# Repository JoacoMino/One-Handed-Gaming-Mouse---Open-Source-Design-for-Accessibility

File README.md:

# One-Handed-Gaming-Mouse---Open-Source-Design-for-Accessibility
Open source files for a low-cost gaming mouse with one-handed use. Includes 3D models, PCB schematics, firmware, and assembly guides to improve gaming accessibility for people with reduced mobility.

# One-Handed Gaming Mouse — Open Source Design for Accessibility

Open source files for a low-cost, one-handed gaming mouse. Includes 3D models, PCB schematics, firmware (Arduino IDE) and assembly guides. Designed to improve gaming accessibility for people with reduced mobility.

## Features
- Fully 3D printable chassis
- Modular design for easy assembly and repair
- Arduino-based firmware (mode: WASD)
- Open source PCB schematics

## Acknowledgements
This project incorporates firmware elements from the PMW3360 module by CitizenJoe (https://www.tindie.com/products/citizenjoe/pmw3360-motion-sensor/), included with purchase of the module and used with permission.

## License
This repository is released under the MIT License. You are free to use, modify, and distribute it for personal or commercial use, provided you include proper attribution.

## Links
- [Project documentation (PDF)](link)
- [Bill of Materials](link)

## Notes
For links to components and suppliers, see the dedicated section in the documentation or in the repository.

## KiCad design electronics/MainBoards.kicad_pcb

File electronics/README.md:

# Electronics

This folder contains the PCB designs and schematics for the project.

## Included files

- **main-board.sch / .pcb**: Main PCB with the SparkFun Pro Micro, PMW3360 sensor, and connectors.
- **matrix-board.sch / .pcb**: PCB for the 3×4 matrix of mechanical key switches.

## Manufacturing

These PCBs were designed using KiCAD and ordered from a factory in China. Assembly requires:

- Soldering hotswap sockets for key switches.
- Soldering diodes (1N4007 DC) on the matrix board.
- Installing the SparkFun Pro Micro and PMW3360 sensor.

## Components

- 1 SparkFun Pro Micro
- 1 PMW3360 optical sensor module
- 11 Mechanical key switches
- 11 Hotswap sockets
- 11 Diodes 1N4007 DC
- JST connectors for modular assembly

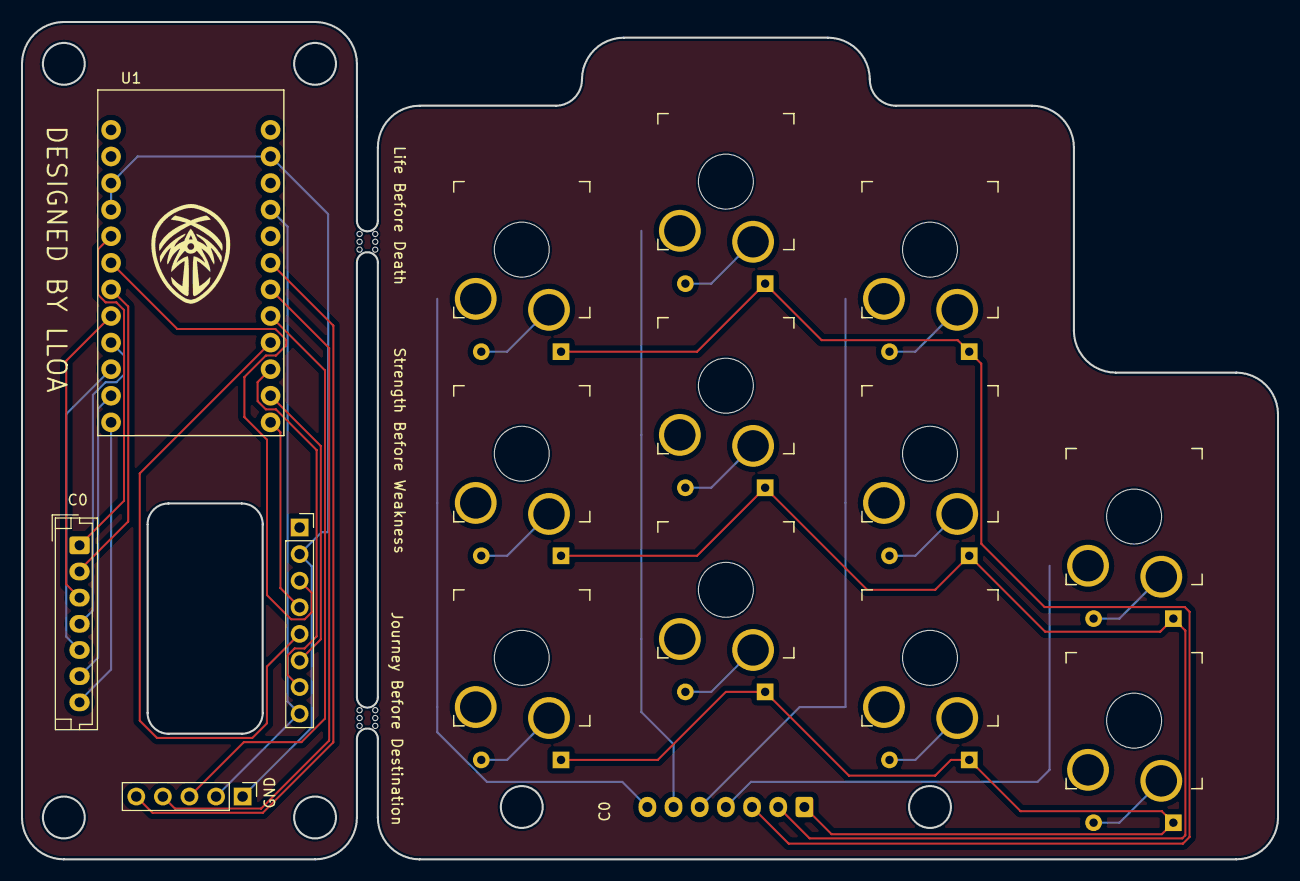
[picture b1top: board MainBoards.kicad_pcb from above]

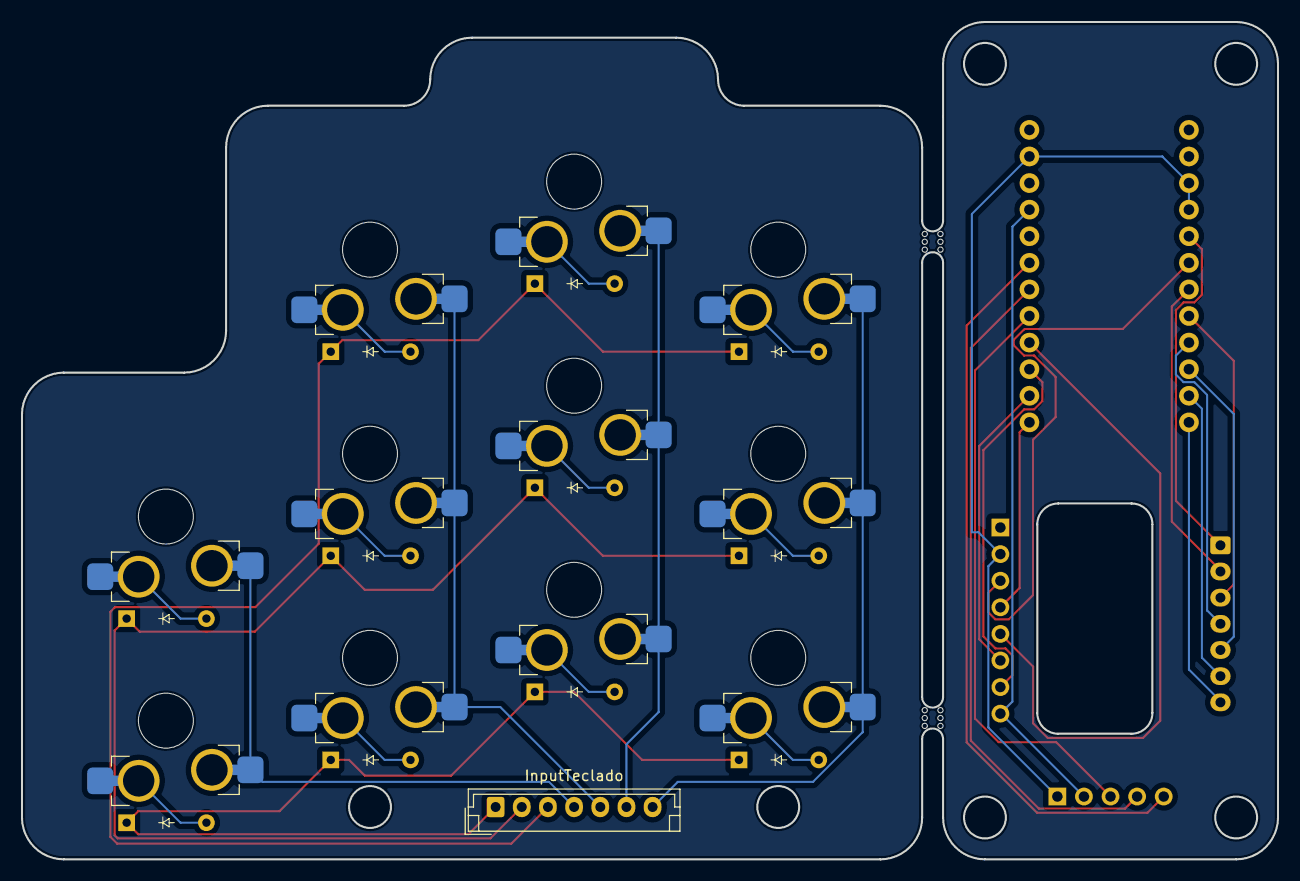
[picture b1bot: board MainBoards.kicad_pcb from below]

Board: 2 copper layers, 120.0 x 80.0 mm, 29 parts (12 on the bottom side), 35 nets.

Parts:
D1, D2, D3, D4, D5, D6, D7, D8, D9, D10, D11: Diode; Diode_DO-35
InputTeclado: Conn_01x07_Socket; JST_EH_B7B-EH-A_1x07_P2.50mm_Vertical
J2: MouseModule; PinSocket_1x08_P2.54mm_Vertical
J4: JoyStickModule; PinHeader_1x05_P2.54mm_Vertical
J5: OutputTeclado; JST_EH_B7B-EH-A_1x07_P2.50mm_Vertical
S1, S2, S3, S4, S5, S6, S7, S8, S9, S10, S11: Keyswitch; SW_Gateron_LowProfile_HotSwap_PTH
U1: DEV-12587; MODULE_DEV-12587
mouse-bite-2mm-slot, mouse-bite-2mm-slot#2: VAL**; mouse-bite-2mm-slot

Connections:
Column 0: J5.1, U1.JP7_8 (D2)
Column 0 IN: InputTeclado.7, S1.1, S4.1, S8.1
Column 1: J5.2, U1.JP7_6 (D4)
Column 1 IN: InputTeclado.6, S2.1, S5.1, S9.1
Column 2: J5.3, U1.JP7_5 (D5)
Column 2 IN: InputTeclado.5, S3.1, S6.1, S10.1
Column 3: J5.4, U1.JP7_4 (D6)
Column 3 IN: InputTeclado.4, S7.1, S11.1
GROUND: J2.2, J4.1, U1.JP6_2 (GND), U1.JP7_9 (GND), U1.JP7_10 (GND)
MisoModu: J2.7, U1.JP6_10 (MISO)
MosiModu: J2.6, U1.JP6_11 (MOSI)
MtModu: J2.3, U1.JP7_7 (D3)
NcsModu: J2.4, U1.JP6_12 (D10)
unnamed: D1.2 (A), S1.2
unnamed: D2.2 (A), S2.2
unnamed: D3.2 (A), S3.2
unnamed: D4.2 (A), S4.2
unnamed: D5.2 (A), S5.2
unnamed: D6.2 (A), S6.2
unnamed: D7.2 (A), S7.2
unnamed: D8.2 (A), S8.2
unnamed: D9.2 (A), S9.2
unnamed: D10.2 (A), S10.2
unnamed: D11.2 (A), S11.2
Row 0: J5.5, U1.JP7_3 (D7)
Row 0 IN: D1.1 (K), D2.1 (K), D3.1 (K), InputTeclado.3
Row 1: J5.6, U1.JP7_2 (D8)
Row 1 IN: D4.1 (K), D5.1 (K), D6.1 (K), D7.1 (K), InputTeclado.2
Row 2: J5.7, U1.JP7_1 (D9)
Row 2 IN: D8.1 (K), D9.1 (K), D10.1 (K), D11.1 (K), InputTeclado.1
SW JS: J4.5, U1.JP6_6 (A2)
SckModu: J2.5, U1.JP6_9 (SCK)
VRX JS: J4.3, U1.JP6_8 (A0)
VRY JS: J4.4, U1.JP6_7 (A1)
Vin: J2.8, J4.2, U1.JP6_4 (VCC)

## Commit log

2025-06-02 LICENSE
2025-06-02 README.md
2025-06-02 Firmware_README.md
2025-06-02 Electronics_README.md
2025-06-02 3DModels_README.md
